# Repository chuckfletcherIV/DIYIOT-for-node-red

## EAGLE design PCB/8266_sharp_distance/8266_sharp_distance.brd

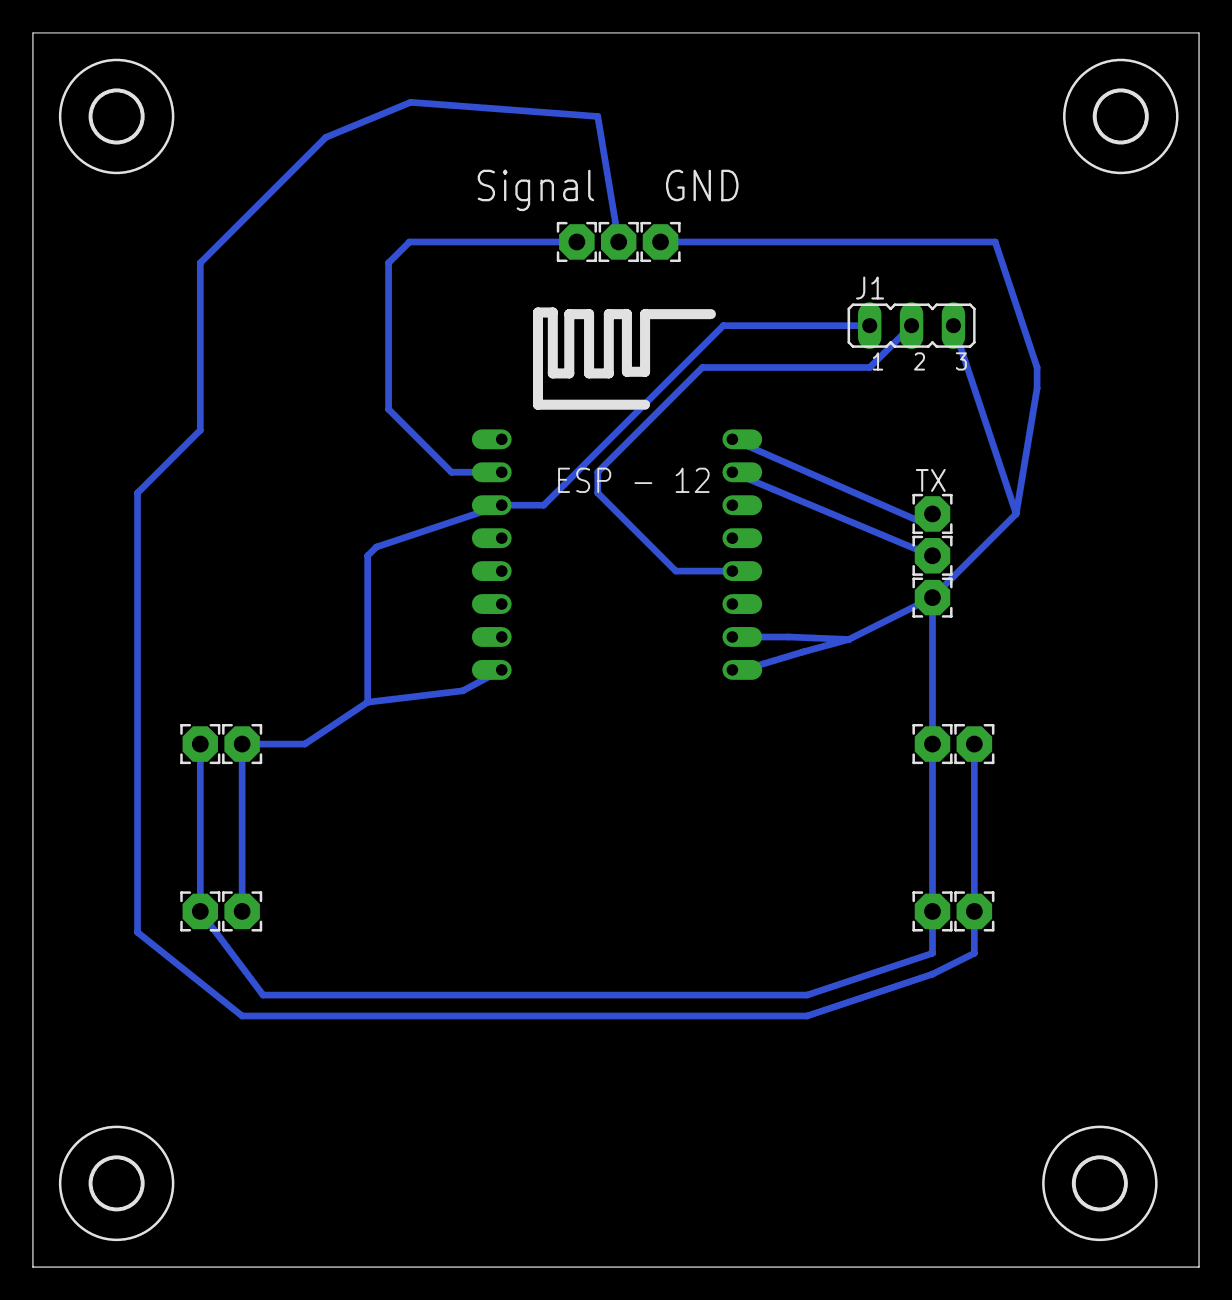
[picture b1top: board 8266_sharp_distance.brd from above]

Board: 2 copper layers, 70.8 x 74.9 mm, 20 parts (0 on the bottom side), 6 nets.

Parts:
3.3V_1, 3.3V_2, 5V, 5V_2, 5V_POT: 2,15/1,0
GND: 2,15/1,0
GND_1, GND_2, GND_3, GND_4: 2,15/1,0
GND_POT: 2,15/1,0
J1: JP2
POT_SIGNAL: 2,15/1,0
RX: 2,15/1,0
TX: 2,15/1,0
U$1, U$2, U$5, U$6: 3,0
U$4: ESP12

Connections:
5V: 5V.1, 5V_2.1, 5V_POT.1, GND.1, GND_1.1, GND_2.1, GND_3.1, GND_4.1, GND_POT.1, J1.3, U$4.GND, U$4.GPIO15
unnamed: J1.2, U$4.GPIO0
unnamed: POT_SIGNAL.1, U$4.ADC
unnamed: 3.3V_1.1, 3.3V_2.1, J1.1, U$4.CH_PD, U$4.VCC
RX: RX.1, U$4.RX
TX: TX.1, U$4.TX
